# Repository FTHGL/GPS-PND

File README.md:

# GPS PND Project

This repository contains the KiCad design files and documentation for the GPS PND (Portable Navigation Device) project. The design includes a power supply circuit, STM32F301K6 microcontroller, and the MS38SN4 GNSS module, aimed at providing GPS functionality for various IoT and navigation applications.

## Features

### Power Supply: AZ1117-3.3
- Stable 3.3V output for powering the MCU and GNSS module.
- Low dropout regulator with thermal shutdown and overcurrent protection.
- [More Information - AZ1117-3.3](https://www.google.com/url?sa=t&source=web&rct=j&opi=89978449&url=https://www.diodes.com/assets/Datasheets/products_inactive_data/AZ1117.pdf&ved=2ahUKEwjyg4W8j6yJAxUHLrkGHUjTN9YQFnoECAwQAQ&usg=AOvVaw0PLg3CQl6F88jSyHaR0euA)

### Microcontroller: STM32F301K6
- ARM Cortex-M4 operating at 72 MHz with FPU for enhanced processing.
- 32 KB Flash memory and 16 KB SRAM.
- Connected to various peripherals such as USART, which is used both for communication and boot processes, and GPIO, which is used for control and to handle the PPS interrupt signal from the GNSS module.
- [More Information - STM32F301K6](https://www.st.com/en/microcontrollers-microprocessors/stm32f301k6.html)

### GNSS Module: MS38SN4
- Multi-constellation GNSS receiver: GPS, Beidou, Glonass, Galileo.
- Ultra-low power consumption for battery-operated devices.
- Integrated PPS (Pulse Per Second) output for precise synchronization.
- [More Information - MS38SN4](https://en.minewsemi.com/gnss-module/ms38sn4)

## Requirements

### Hardware:
- AZ1117-3.3V Low Dropout Regulator
- STM32F301K6U6 ARM Cortex-M4 Microcontroller
- MS38SN4 GNSS Module

### Software:
- KiCad for PCB design
- STM32CubeIDE or Keil for programming the microcontroller
- GNSS data parsing libraries (optional, depending on application) [More Information - MS38SN4](https://en.minewsemi.com/gnss-module/ms38sn4)

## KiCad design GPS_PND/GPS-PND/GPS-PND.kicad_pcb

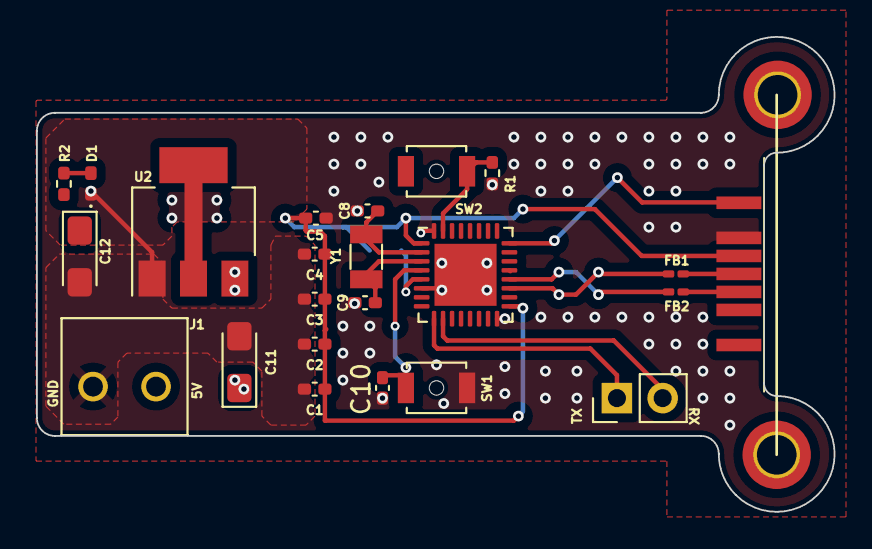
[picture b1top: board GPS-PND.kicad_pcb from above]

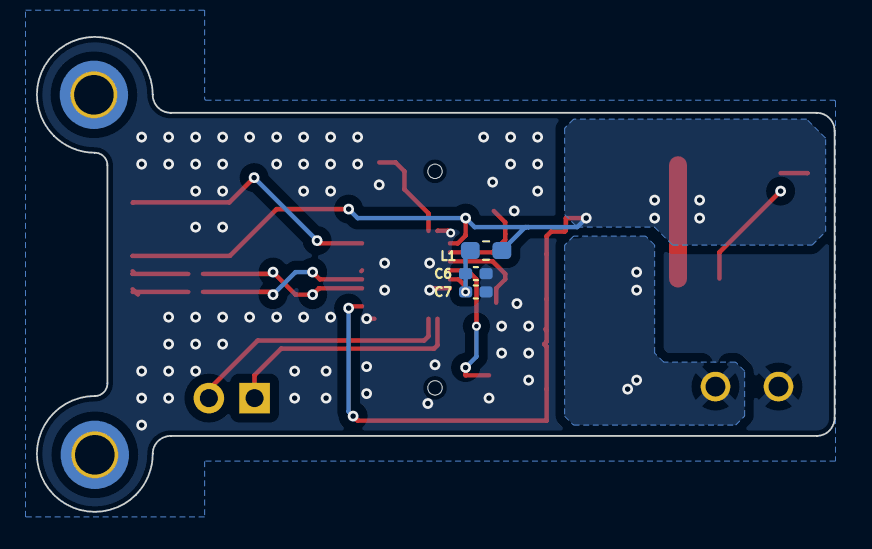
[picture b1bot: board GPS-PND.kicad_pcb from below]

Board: 2 copper layers, 44.3 x 26.4 mm, 26 parts (3 on the bottom side), 16 nets.

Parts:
C1, C2, C3, C4: 100 nF; C_0402_1005Metric_Pad0.74x0.62mm_HandSolder
C5: 4.7 uF; C_0402_1005Metric_Pad0.74x0.62mm_HandSolder
C6: 1 uF; C_0402_1005Metric_Pad0.74x0.62mm_HandSolder
C7: 10 nF; C_0402_1005Metric_Pad0.74x0.62mm_HandSolder
C8: 5 pF; C_0402_1005Metric_Pad0.74x0.62mm_HandSolder
C9, C10: 25 pF; C_0402_1005Metric_Pad0.74x0.62mm_HandSolder
C11: 10 uF; CP_EIA-3216-12_Kemet-S_Pad1.58x1.35mm_HandSolder
C12: 22 uF; CP_EIA-3216-12_Kemet-S_Pad1.58x1.35mm_HandSolder
D1: LED_0402_1005Metric_Pad0.77x0.64mm_HandSolder
FB1, FB2: BLM15HD102SN1; L_0201_0603Metric_Pad0.64x0.40mm_HandSolder
J1: ED555/2DS; ED555_2DS
J2: Conn_01x02; PinHeader_1x02_P2.54mm_Vertical
L1: 27 nH; L_0603_1608Metric_Pad1.05x0.95mm_HandSolder
R1, R2: 4.7k; R_0402_1005Metric_Pad0.72x0.64mm_HandSolder
SW1, SW2: SW_SPST_B3U-1000P-B
U1: STM32F301K6Ux; QFN-32-1EP_5x5mm_P0.5mm_EP3.45x3.45mm
U2: AZ1117-3.3; SOT-223-3_TabPin2
U3: MS38SN4
Y1: 8Mhz; Crystal_SMD_3215-2Pin_3.2x1.5mm

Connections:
5V: C11.1, J1.2, U2.3 (VI)
BOOT0: R1.1, SW2.1, U1.31 (BOOT0)
GND: C1.2, C2.2, C3.2, C4.2, C5.2, C6.1, C7.1, C8.2, C9.2, C10.2, C11.2, C12.2, D1.1 (K), J1.1, R1.2, SW1.1, U1.6 (VSSA), U1.16 (VSS), U1.32 (VSS), U1.33 (VSS), U2.1 (GND), U3.6 (GND)
NRST: C10.1, SW1.2, U1.4 (NRST)
unnamed: D1.2 (A), R2.2
unnamed: FB1.1, U3.4 (RXD)
unnamed: FB2.1, U3.3 (TXD)
OSC_IN: C8.1, U1.2 (PF0), Y1.2
OSC_OUT: C9.1, U1.3 (PF1), Y1.1
PPS(interrupt): U1.24 (PA14), U3.7 (PPS(Second_pulse))
USART1_rX: FB2.2, U1.20 (PA10)
USART1_tX: FB1.2, U1.19 (PA9)
USART2_rX: J2.2, U1.10 (PA3)
USART2_tX: J2.1, U1.9 (PA2)
VBAT: C1.1, C2.1, C3.1, C4.1, C5.1, C12.1, L1.1, R2.1, SW2.2, U1.1 (VDD), U1.17 (VDD), U2.2 (VO), U3.5 (GPS_VCC)
VDDA: C6.2, C7.2, L1.2, U1.5 (VDDA)

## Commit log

2024-10-26 Gloabal Positioning System Personal Navigation Device
2024-10-26 a series of changes
2026-01-18 added soma changes
